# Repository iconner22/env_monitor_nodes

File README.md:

## Project Overview
This project implements **multihop, ad-hoc wireless sensor network (WSN)** for environmental monitoring. The system is built around Arduino UNO nodes that communicate using a 915 MHz transciever and a centeral gateway that handles requests and data storage. The gateway node requests temperature and humidity at sent intervals and collects sound data based on a monitored threshold. The network performs a discovery upon initialization which allows for ad-hoc distribution and supports multi-hop communication based on a path supplied by the gateway.

## Hardware
The system is built off of Arduino UNOs and custom PCB shields which integrate the RF transciever and sensors into the microcontroller.

<figure>
  
  <figcaption>Custom PCB for Sensor Nodes.</figcaption>
</figure>

<figure>
  
  <figcaption>Custom PCB for Communication and Gateway Nodes.</figcaption>
</figure>

## Node Types

The network is composed of three distinct node roles: **sensor nodes**, **communication nodes**, and a **gateway node**. All nodes share a common hardware and software base, with behavior determined by role-specific logic and sensors.

### Sensor Nodes
<figure>
  
  <figcaption>Assembled Sensor Node.</figcaption>
</figure>
Sensor nodes are responsible for collecting and reporting environmental data. These nodes interface with temperature, humidity, and sound sensors.

Sensor nodes:
- Respond to gateway-initiated requests for environmental or GPS data
- Participate in network discovery and routing
- Transmit sound data upon trigger
- Prioritize low-power operation during idle periods

### Communication Nodes
<figure>
  
  <figcaption>Assembled Communication Node.</figcaption>
</figure>
Communication nodes help in the routing and localization of the network.

Communication nodes:
- Participate fully in discovery and routing
- Forward packets between sensor nodes and the gateway
- Maintain routing state during the discovery phase
- Improve network robustness and multihop coverage
- Record GPS coordinates used in trilateration

### Gateway Node
<figure>
  
  <figcaption>Assembled Gateway Node.</figcaption>
</figure>
The gateway node serves as the **root of the network** and the primary interface between the WSN and external systems. The Arduino UNO is connected to a RasperryPi which handles the routing protocols and publishing of data.

The gateway:
- Initiates network discovery and route construction
- Requests environmental and GPS data from sensor nodes
- Receives asynchronous event-driven messages
- Aggregates data for storage in an external database
- Acts as the final destination for routed transmissions

## Network Architecture

The network operates as a **fully ad-hoc, multihop mesh**. Nodes do not rely on preconfigured routing tables; instead, routes are dynamically discovered during a **network setup (discovery) phase**.

The network supports both:
- **Request–response communication** initiated by the gateway (e.g., environmental or GPS data)
- **Asynchronous event-driven messages**, such as sound-triggered alerts that propagate back toward the gateway

## Discovery and Routing Algorithm
During the discovery process, the gateway node performs **Dijkstra’s algorithm** using the RSSI as the edge cost, a 32-bit integer is used to represent each node in the network where a 1 signals that it needs to be explored and a 0 signals that it already has been explored. This allows for a compact representation of 32 nodes, and the use of bitwise operations during the discovery process. The gateway node then stores a routing table, and upon request transmits the necessary path to the destination node. For the event based transmissions, each of the nodes stores the best path back to the gateway and transmits over this. The transmissions are handled using a baseline struct which is able to store the required data for each transmission type. The transmission is signified using an enum that specifies the type of tranmission and if it is a request or response. 

## Transmission Structure

```cpp
enum TransmissionType {
  DISCOVERY_REQUEST,
  GPS_REQUEST,
  ENV_SENSOR_REQUEST,
  DISCOVERY_RESPONSE,
  SOUND_RESPONSE,
  GPS_RESPONSE,
  ENV_SENSOR_RESPONSE,
  DISCOVERY_RESPONSE_FINISHED,
  WEIGHT_CALCS
};

/********* Transmission Struct ********/
struct TransmissionData{
    int dest;
    int curr_num_hops;
    int path[MAX_HOPS+1];
    float dataOne; // temp, latitude, RSSI
    float dataTwo; // humidity, longitude, timing
    TransmissionType dataType;
    uint32_t nodeClosedOpenEncoding; // 1 = node unvisited, 0 = visited
};
````

## Included in this repository
This repository includes the PCB design and all of the Arduino code required for the sensor, communication, and gateway nodes. Additional code is needed for the RaspberryPi to communicate with the gateway arduino. This is what handled the discovery process.

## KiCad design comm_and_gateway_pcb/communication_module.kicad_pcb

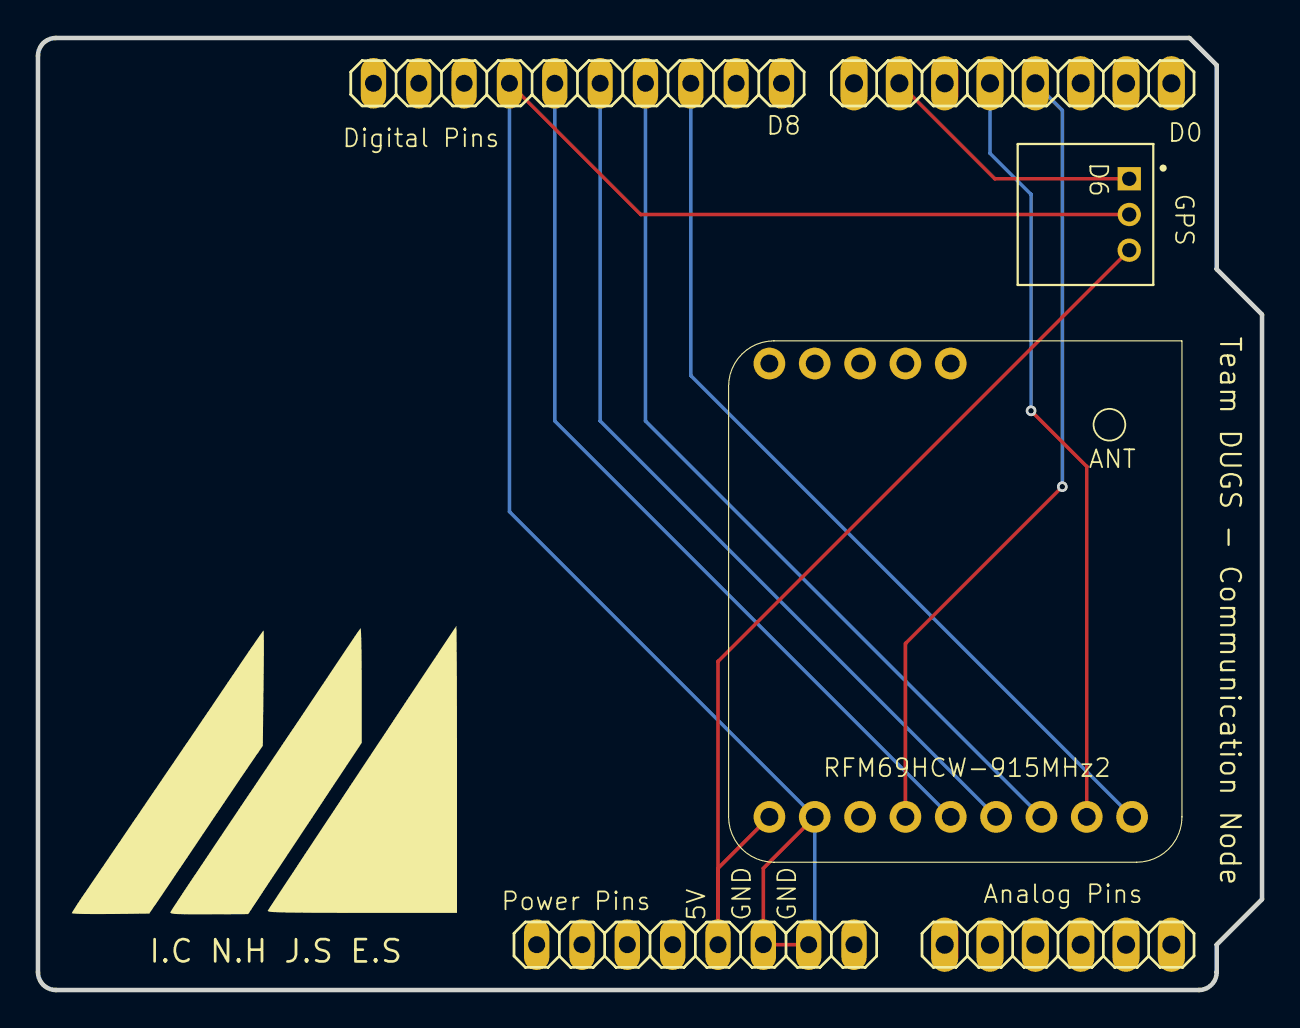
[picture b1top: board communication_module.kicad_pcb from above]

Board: 2 copper layers, 68.6 x 53.3 mm, 6 parts (0 on the bottom side), 9 nets.

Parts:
ANALOG-1: PINHD-1X6; ANALOG_PINS
DIGITAL-H2: Digital_Top; DIGITAL_TOP_PINS
DIGITAL-L2: Digital_Bottom; DIGITAL_BOTTOM
J2: 61300311121; JST_S3B-PH-K-S_LF__SN_
POWER1: PINHD-1X8TH; POWER_PINS
RFM69HCW-915MHz2: RF69_MODULE

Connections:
/5V: J2.3, POWER1.5, RFM69HCW-915MHz2.1 (Vin)
/D3: DIGITAL-L2.5, RFM69HCW-915MHz2.4 (G0)
/D4: DIGITAL-L2.4, RFM69HCW-915MHz2.8 (CS)
/D6: DIGITAL-L2.2, J2.1
/D10: DIGITAL-H2.3, RFM69HCW-915MHz2.9 (RST)
/D11: DIGITAL-H2.4, RFM69HCW-915MHz2.7 (MOSI)
/D12: DIGITAL-H2.5, RFM69HCW-915MHz2.6 (MISO)
/D13: DIGITAL-H2.6, RFM69HCW-915MHz2.5 (SCK)
/GND: DIGITAL-H2.7, J2.2, POWER1.6, POWER1.7, RFM69HCW-915MHz2.2 (GND)

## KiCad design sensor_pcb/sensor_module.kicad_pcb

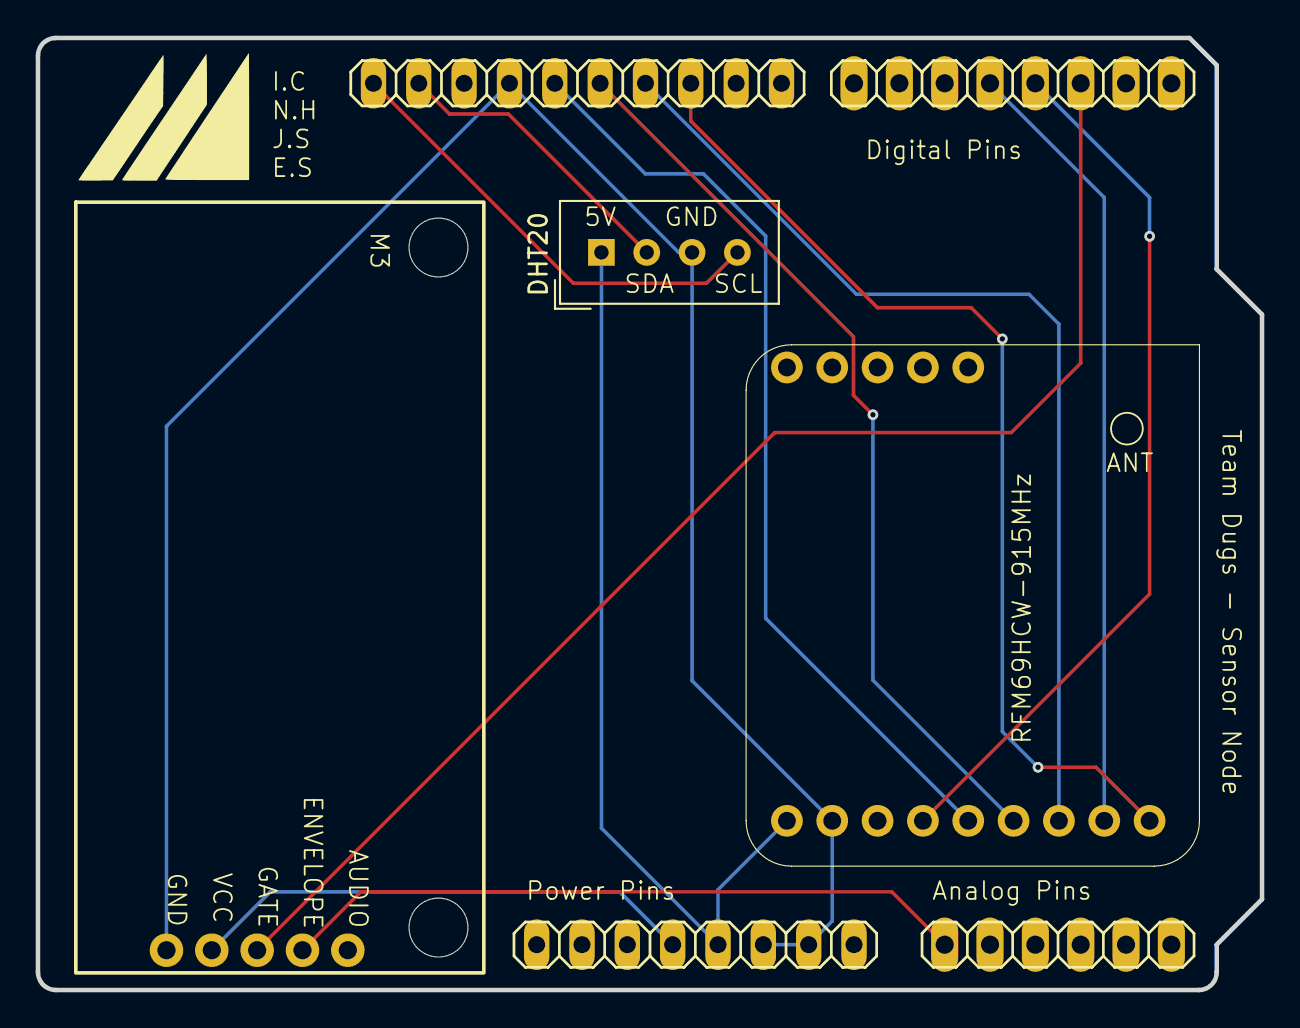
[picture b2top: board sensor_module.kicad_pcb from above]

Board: 2 copper layers, 68.6 x 53.3 mm, 7 parts (0 on the bottom side), 13 nets.

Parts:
ANALOG-1: Analong Pins; ANALOG_PINS
DHT20: DHT20; DHT20-Temp-Humidity
DIGITAL-H1: Digital_Top; DIGITAL_TOP_PINS
DIGITAL-L1: Digital_Bottom; DIGITAL_BOTTOM
POWER1: Power_Pins; POWER_PINS
RFM69HCW-915MHz: RF69_MODULE
SOUND_BOB1: SOUND-BOB

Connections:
/3.3V: POWER1.4, SOUND_BOB1.2 (VCC)
/5V: DHT20.1 (VDD), POWER1.5, RFM69HCW-915MHz.1 (Vin)
/A0: ANALOG-1.1, SOUND_BOB1.4 (ENVELOPE)
/D2: DIGITAL-L1.6, SOUND_BOB1.3 (GATE)
/D3: DIGITAL-L1.5, RFM69HCW-915MHz.4 (G0)
/D4: DIGITAL-L1.4, RFM69HCW-915MHz.8 (CS)
/D10: DIGITAL-H1.3, RFM69HCW-915MHz.9 (RST)
/D11: DIGITAL-H1.4, RFM69HCW-915MHz.7 (MOSI)
/D12: DIGITAL-H1.5, RFM69HCW-915MHz.6 (MISO)
/D13: DIGITAL-H1.6, RFM69HCW-915MHz.5 (SCK)
/GND: DHT20.3 (GND), DIGITAL-H1.7, POWER1.6, POWER1.7, RFM69HCW-915MHz.2 (GND), SOUND_BOB1.1 (GND)
/SCL: DHT20.4 (SCL), DIGITAL-H1.10
/SDA: DHT20.2 (SDA), DIGITAL-H1.9

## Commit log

2025-10-25 files
2025-10-25 added into folders and removed proj specific files
2025-10-25 Arduino code added
2026-01-19 imgs added
2026-01-19 missing img
2026-01-19 Add project overview and detailed README
    This README provides an overview of the multihop, ad-hoc wireless sensor network project, detailing hardware, node types, network architecture, and transmission structure.
